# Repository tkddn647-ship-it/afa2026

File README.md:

# AFA2026 계측 시스템

학생 포뮬러 전기차(아주대학교 A-FA)의 **실차 데이터 계측 시스템**입니다.
서스펜션·가속도·인버터/BMS·조향 데이터를 STM32 한 곳에서 같은 시간축으로 모으고, Raspberry Pi를 거쳐 서버에 기록·실시간 표시·카메라 녹화까지 연결합니다.

| 항목 | 내용 |
|------|------|
| 기간 | 2025.09 ~ 2026.08 |
| 역할 | 계측 파트장 (계측 파트 2인) |
| 하드웨어 | STM32F407, Raspberry Pi 5, Cascadia 인버터 · Orion BMS 2 · Bosch LWS (CAN) |
| 소프트웨어 | C (STM32 HAL, DMA), Python (FastAPI 서버, 분석), JavaScript (대시보드) |

## 주요 결과

| 항목 | 결과 |
|------|------|
| 데이터 운용 주기 | 전송 방식을 WebSocket → UDP/TCP로 바꾸고 MCU에 링버퍼 + DMA 적용, **10 Hz → 100 Hz** |
| 신호 오류 판정 | 실주행 로그 3개(74,062행)에서 인버터 DC 전류가 팩 전류보다 약 25% 크게 기록된 것을 발견, 비율 0.80 재현으로 **CAN 스케일 계수 누락** 규명, 보정 계수 1.25 도출 |
| 계측 정확도 | 섀시 다이나모 교차 검증: 최고속도 계측 90 km/h vs 다이나모 87 km/h (**오차 약 3.4%**) |
| EMI 대응 | HV 동작 시 튀는 센서 값을 HV ON/OFF 시점 대조로 전자기 간섭으로 규명, 신호선 분리 · 차폐로 해결 |
| 분석 도구 | 주행 로그와 카메라 영상을 같은 시간축으로 맞춰 보는 도구를 만들어 섀시 · 파워트레인 파트가 주행 분석에 사용 |

## 남은 과제

- **데이터 무결성**: 로그별 샘플 누락 5~10%, 깨진 행 최대 약 0.1% → 바이너리 패킷 + CRC + 시퀀스 번호로 수신 즉시 판별
- **절대값 검증**: 두 전류의 비율은 맞췄지만 어느 쪽이 절대적으로 정확한지는 미검증 → 클램프 미터로 독립 측정
- **보안**: 팀 내부 전용이라 성능을 우선했음 → 열린 포트 최소화, SSH 키 인증, 방화벽 적용
- 펌웨어 RTOS 전환, 리니어 센서 전원 강하 원인 특정 (아래 §11, §4.2)

## 저장소 구성

| 경로 | 내용 |
|------|------|
| `device/ECU_test/` | STM32CubeIDE 프로젝트 (메인 MCU 펌웨어) |
| `device/raspberry pi 5/` | UART 수신 · 서버 전송 · 카메라 업로드 |
| `server/` | 로깅(`udp_logger`), 실시간 대시보드(`udp_realtime`), 분석 서버(`analysis_server`) |
| `hardware/26_TELEPCB/` | 텔레메트리 보드 KiCad 회로도 · PCB · 거버 |

아래부터는 다음 담당자를 위한 **설계 의도와 구현 구조** 문서입니다.

---

## 1. 한 줄 요약

> 차량의 리니어·가속도·인버터/BMS·조향 데이터를 **MCU에서 동일 타임라인으로 통합 수집(100 Hz)** 하고, UART로 Raspberry Pi에 넘겨 Hotspot Wi‑Fi로 서버에 로깅·실시간 표시·카메라 녹화까지 연결한다.  
> (현재 구현 보드는 STM32F407이며, **시간 동기화가 목적이라 Teensy 등 다른 MCU로 대체 가능** — 자세한 내용은 §5.2)

---

## 2. 전체 시스템 구조

```
[차량 센서/ECU들]                    [현장 보드]                         [네트워크]         [서버]
Linear FR/FL/RR/RL ──ADC──┐
LIS3DSH Accel ──────SPI───┤
Motor Inverter+BMS ─CAN1──┼──▶ STM32F407 MCU ──UART4 921600──▶ Raspberry Pi 5 ──Wi‑Fi──▶ Hotspot
Steering (LWS) ─────CAN2──┘         ▲                              │ Camera 15fps              │
Wheel speed (옵션) ─USART2─┘         │                              │                           ▼
                                      │                         data_send_server.py     Logger   :8000
                                      └─ 모든 텔레메트리 1차 집약                         Realtime :8011
                                                                                         Camera   :8012
```

설계의 핵심은 **“모든 차량 데이터는 먼저 MCU로 모인다”** 입니다.

| 구간 | 역할 |
|------|------|
| 센서 / CAN | 물리량·차량 버스 데이터 생성 |
| **STM32 MCU** | 샘플링·단위 환산·버퍼링·동기 타임스탬프 |
| **UART4** | MCU → Pi 단일 CSV 스트림 |
| **Raspberry Pi 5** | 파싱, 배치 HTTP 전송, 카메라 프레임 업로드 |
| **Hotspot** | 이동 환경 Wi‑Fi (아이폰 핫스팟 등으로 운용) |
| **서버** | 집 노트북에서 구동. CSV 로깅, 실시간 대시보드, 카메라 수신/녹화. 공유기 포트포워딩 + SSH로 원격 관리 |

배치도 이미지: [`afa2026_system_layout.png`](./afa2026_system_layout.png)

서버는 클라우드 전용 VM이 아니라 **집에 둔 노트북**을 서버로 쓰고, 공유기·방화벽·SSH를 열어 **밖에서도 본인 PC로 원격 접속·제어**하는 방식으로 운용했습니다. 자세한 절차는 [§8. 집 서버 원격 접속 (포트포워딩 + SSH)](#8-집-서버-원격-접속-포트포워딩--ssh) 참고.

---

## 3. 하드웨어 설계

### 3.1 MCU 보드

| 항목 | 내용 |
|------|------|
| MCU | **STM32F407** (Discovery / 커스텀 PCB 연동) |
| 클럭 | HSE 크리스털 → PLL (시스템 클럭). UART/CAN 비트 타이밍 정확도에 필요 |
| 워치독 | IWDG (~1 s) — 메인 루프 정지 시 리셋 |

### 3.2 센서·버스 핀맵 (펌웨어 기준)

#### 리니어 포텐셔미터 (서스펜션 변위)

| 채널 | MCU 핀 | ADC | 비고 |
|------|--------|-----|------|
| **FR** | PA1 | ADC1_IN1 | 3선: VCC / GND / Signal |
| **RR** | PA2 | ADC1_IN2 | |
| **RL** | PA3 | ADC1_IN3 | |
| **FL** | PA4 | ADC1_IN4 | |

- ADC 기준(VDDA)은 **3.3 V**
- 센서 공급/풀스케일 전압은 채널별로 다르며, **소프트웨어 vmax 캘리브레이션**으로 0–100 mm에 맞춤
- Discovery **PA0**은 유저 버튼용이라 리니어에 사용하지 않음

#### 가속도

| 센서 | 인터페이스 | 비고 |
|------|------------|------|
| LIS3DSH | SPI1 | ODR 상향(400 Hz급)으로 200/100 Hz 샘플에 대응 |

#### CAN

| 버스 | 속도 | 핀 (펌웨어) | 상대 |
|------|------|-------------|------|
| **CAN1** | 250 kbps | **PB8 RX / PB9 TX** | Cascadia 인버터 + Orion BMS |
| **CAN2** | 500 kbps | **PB12 / PB13** | Bosch LWS 조향 |

> 회로도/PCB와 핀이 어긋나면(예: CAN1이 PA11/PA12로만 배선) 수신이 안 됩니다. 펌웨어는 **PB8/PB9, PB12/PB13** 기준입니다.

#### UART

| 포트 | 보드레이트 | 핀 | 용도 |
|------|------------|-----|------|
| **UART4** | **921600** | PC10 TX / PC11 RX | Raspberry Pi 텔레메트리 |
| USART2 | 115200 | (휠스피드 아두이노 등) | 옵션 |

Pi 배선 (GPIO):

| STM32 | Raspberry Pi 5 |
|-------|----------------|
| PC10 (UART4 TX) | Pin 10 (GPIO15 RX) |
| PC11 (UART4 RX) | Pin 8 (GPIO14 TX) |
| GND | GND |

포트: `/dev/ttyAMA0` (`dtparam=uart0=on`)

### 3.3 전원·배치·실차 이슈 (설계 시 고려)

- MCU·Pi는 근거리(배전함 등)에 두고, 모터컨트롤러는 함 밖인 경우가 많음 → **UART 거리는 짧아 유리**, 다만 **고전류 GND/EMI**가 케이블로 타고 들어옴
- 리니어 케이블에서 **신호↔파워 교차/단락** 시 중간 위치에서도 ADC가 ~3.3 V(100 mm 고정)처럼 보임 → 하드웨어 배선 문제로 확인됨
- 플로팅 ADC 핀은 센서 미연결 시에도 중간값이 움직임 → 정상 현상
- 핫스팟 + 차량 이동 시 **Pi→서버 업로드**가 병목이 되어 로그 유효 Hz가 떨어질 수 있음 (MCU 샘플링과 별개)

---

## 4. 소프트웨어 아키텍처 (device)

### 4.1 디렉터리

```
device/
├── ECU_test/                 # STM32CubeIDE 프로젝트 (메인 MCU 펌웨어)
│   ├── Core/Inc|Src/         # 애플리케이션 코드
│   ├── Drivers/              # HAL / CMSIS
│   └── ECU_test.ioc          # CubeMX 설정
├── raspberry pi 5/           # Pi 수신·서버 전송·카메라
│   ├── Uart_stm.py           # UART CSV 파서
│   ├── data_send_server.py   # ingest / realtime 전송
│   ├── camera.py             # 카메라 프레임 업로드 (15fps 운용)
│   └── stm_ingest.env.example
├── wheel_speed/              # 휠스피드 아두이노 (옵션)
├── Fluid_Sensor/             # 유체 센서 스케치
├── esp32/ , esp32_motor_can/ # 보조/실험용
└── ...
```

### 4.2 STM32 펌웨어 — 슈퍼루프 설계

RTOS 없이 **메인 루프 + 논블로킹** 구조입니다 (`main.c`).

1. `MX_*_Init` — GPIO, CAN1/2, UART, ADC, SPI, DMA
2. `LIS3DSH` / `CAN_Vehicle` / `CAN_LWS` / `SensorUart` / `Uart4Tx` 초기화
3. 루프:
   - CAN FIFO 드레인·파싱
   - `SensorUart_Process()` — 100 Hz 샘플 적재, 20 Hz DMA flush
   - IWDG kick

#### 샘플링 / 전송

| 항목 | 값 | 파일 |
|------|-----|------|
| 샘플 주기 | **10 ms (100 Hz)** | `sensor_uart.h` / `.c` |
| UART flush | **20 Hz**, 배치 5샘플 | 동일 |
| TX | UART4 **DMA 논블로킹** | `uart4_tx.c` |
| Baud | **921600** | `usart.c` |

초기에는 200 Hz(5 ms)였으나, 실차·무선 부하를 고려해 **100 Hz**로 조정했습니다.

#### 리니어 ADC 처리 (`adc.c` / `adc.h`)

1. 채널당 **8회 평균**
2. **EMA** 필터 (노이즈 완화)
3. 전압 환산: `voltage_mv = raw × 3300 / 4095`
4. 위치 환산(채널별):

```text
position_mm = (voltage_mv / ADC_LINEAR_VMAX_xx_MV) × 100
```

풀 스트로크 실측으로 vmax를 맞춥니다. (예: 풀에서 88.6 mm가 나오면 `vmax_new = vmax_old × 0.886`)

최신 캘리 상수 예:

| 채널 | `ADC_LINEAR_VMAX_*_MV` |
|------|------------------------|
| FR | 1825 |
| RR | 1835 |
| RL | 1827 |
| FL | 1818 |

미해결 이슈 — ADC형 센서 전원 강하 원인 규명 필요: 리니어 포텐셔미터 전원부에서 3A 레귤레이터 Vout 자체는 3.3V로 정상이었으나, PCB를 지나 센서 커넥터 단에서는 2.3~2.7V까지 떨어지는 현상이 실측됐습니다. 흐르는 전류가 mA 수준(저항 분압 구조)인 점을 감안하면 컨버터 용량 부족은 아니며, Vout 이후 구간(PCB 파워 트레이스 또는 커넥터 접점)에서 비정상적으로 큰 저항이 있는 것으로 추정되는데 이게 어디가 문제인지 정확하게 확인을 못해서 소프트웨어적으로 캘리브레이션 우선 했습니다. 이 전압 강하가 vmax 캘리브레이션을 흔드는 원인이 될 수 있어, 트레이스 문제인지 커넥터 접점 문제인지 다음 담당자가 실측으로 특정해야 하는 미해결 문제입니다.

#### CAN 파싱 (`can_vehicle.c`, `can_lws.c`)

- Cascadia Motion 프로토콜(V5.9 계열): 온도·전류·전압·토크·Id/Iq·RPM 등 **int16 × 0.1** 환산 후 float 보관
- Orion BMS 커스텀 ID(0x081/0x082 등): 전압·전류·Ah·온도·CCL/DCL
- LWS: 조향각·조향 속도
- UART로 나가기 전에 **이미 공학 단위로 환산**됨 (Pi/서버에서 재스케일하지 않음)
- `can1` / `can2`: 최근 **500 ms** 내 수신 여부 (0/1)

#### UART CSV 한 줄 (순서 고정)

```text
stm_ms, FR, FL, RR, RL, x_g, y_g, z_g, ecu_temp,
steering_angle, steering_speed,
inv_temp_igt, inv_temp_motor, inv_motor_speed, inv_dc_current, inv_voltage,
motor_precharge, motor_main_contactor, motor_inverter_mode,
inv_shudder_torque, inv_id_feedback, inv_iq_feedback,
inv_torque_commanded, inv_torque_feedback, inv_id_command, inv_iq_command,
bms_charge, bms_voltage, bms_current, bms_ccl, bms_dcl, bms_temp_maxvalue, bms_capacity,
can1, can2
```

제어 라인(데이터 아님): `STM_READY`, `HB,...`, `LWS_CAL,...`

차속은 `inv_motor_speed × 0.0222328` (타이어 외경 460 mm, 감속비 3.9)로 **서버/Pi에서 계산**하는 것을 권장 (UART 필드 추가 불필요).

### 4.3 Raspberry Pi 5

| 스크립트 | 역할 |
|----------|------|
| `Uart_stm.py` | 921600 수신, CSV 파싱, 100 Hz/20 Hz 배치 개념 |
| `data_send_server.py` | 배치를 Logger `:8000/ingest` + (옵션) Realtime `:8011` 로 POST |
| `camera.py` | JPEG 프레임 업로드 (운용 **15 fps**) |
| `uart_test.py` | 보드레이트/배선 점검 |

예시:

```bash
python3 data_send_server.py \
  --port /dev/ttyAMA0 \
  --baud 921600 \
  --realtime-url http://<server>:8011/api/live/ingest
```

환경 변수 예시는 `stm_ingest.env.example` 참고.

### 4.4 서버 쪽 (연동만 요약)

| 서비스 | 포트 | 역할 |
|--------|------|------|
| `udp_logger` | 8000 | CSV 로깅 ingest |
| `udp_realtime` | 8011 | 실시간 대시보드 |
| camera | 8012 | 프레임 수신·녹화(ffmpeg) |

실차에서 로그 유효 Hz가 50대까지 떨어지는 경우, CSV의 `stm_ms`는 대부분 10 ms를 유지하는 반면 wall-clock 초당 행 수만 줄어든 패턴이 많았습니다 → **MCU 샘플링보다 Hotspot/서버 업로드·카메라 부하**가 원인인 경우가 많습니다. 센서 100 Hz를 유지하려면 카메라 fps/해상도를 먼저 낮추는 편이 유리합니다.

---

## 5. 핵심 설계 판단

### 5.1 MCU 중앙 통합 — 핵심은 “시간 동기화”

이 프로젝트에서 MCU(현재 구현은 STM32F407)를 둔 **가장 큰 이유**는 브랜드가 아니라 **시간 동기화**입니다.

- 리니어·가속도·인버터/BMS CAN·조향 CAN을 **서로 다른 장치·주기**로 받으면, 나중에 맞춰도 샘플 시각이 어긋나기 쉽습니다.
- 그래서 **한 MCU의 틱(`stm_ms` / `HAL_GetTick` 계열)으로 모든 채널을 같은 타임라인에 찍어** Pi·서버로 넘기는 구조를 택했습니다.
- Pi는 네트워크·카메라·업로드를 담당하고, **정밀 주기 샘플링·CAN 집약은 MCU**에 두는 역할 분리입니다.

| | 내용 |
|--|------|
| **선택 이유** | 서스펜션·구동·조향을 **동일 타임스탬프**로 맞춤 |
| **장점** | 단일 UART 스트림, 디버그·확장 용이, 실차 EMI 환경에서도 샘플 주기를 MCU가 책임 |
| **리스크** | MCU/UART가 단일 장애점, CSV가 길면 UART·무선 부하 증가 |

### 5.2 STM32를 꼭 고집할 필요는 없음

**“STM이어야만 한다”는 제약은 없습니다.**  
필요한 것은 대략 다음을 만족하는 **실시간 MCU**면 됩니다.

- ADC(리니어) + (가능하면) SPI/I2C 센서
- CAN 1~2채널 (인버터/BMS/조향)
- 안정적인 주기 타이머·타임스탬프
- Pi로 넘길 UART(또는 USB serial 등) 고속 스트림

그래서 예를 들면 아래도 **같은 역할의 중앙 계측 MCU**로 대체·재구현 가능합니다.

| 후보 | 메모 |
|------|------|
| **Teensy** (4.x 등) | 고속 클럭, USB/시리얼 편함, 커뮤니티 센서 예제 많음 |
| **다른 STM32** | 핀맵·Cube 설정만 맞으면 현재 구조와 가장 유사 |
| **ESP32** 계열 | Wi‑Fi 내장이라 Pi를 줄이는 실험도 가능하나, CAN·실시간·EMI는 설계 부담이 달라짐 |
| **기타 Cortex‑M / 보드** | ADC+CAN+UART만 되면 파이프라인 개념은 동일 |

지금 저장소 펌웨어는 **STM32F407 Discovery/Cube 기반**으로 작성된 **한 가지 구현**입니다.  
구조(센서·CAN → MCU 타임라인 → 시리얼 → Pi → 서버)만 유지하면 **Teensy 등 다른 MCU로 포팅해도 설계 의도는 그대로**입니다.

### 5.3 대안이었던 분산 전송

- 센서·카메라를 각자 올리거나 주기만 다르게 하는 방식
- 무선 부하는 나눌 수 있으나 **시각 동기·배선·프로토콜 복잡도**가 커짐 → 본 프로젝트 목표(동기 로깅)와는 덜 맞음

### 5.4 샘플링 100 Hz / UART 921600

- 200 Hz → 100 Hz: 루프·UART·업로드 여유
- 460800 ↔ 921600: 용량 vs EMI/배선 안정성 트레이드오프. 근거리면 921600 가능

### 5.5 리니어 캘리브레이션을 소프트웨어로

- 채널마다 풀전압이 다름 (하드웨어·케이블·장착)
- 코드에서 채널별 `vmax`로 100 mm 맞춤 — **배선 불량(신호/파워 교차)은 캘리로 고칠 수 없음**

### 5.6 텔레메트리 전송 방식의 다른 선택지

계측에서 “차 → 기록 PC/서버”로 데이터를 넘기는 방법은 팀이 제각각이라, **이 저장소 방식(MCU + Pi + Hotspot Wi‑Fi)이 유일한 정답은 아닙니다.**  
크게 보면 아래 세 갈래로 나뉩니다.

#### (A) 상용 데이터로거를 사서 쓰는 경우

- 완성품 로거에 센서/CAN을 꽂고 USB·자체 소프트웨어로 기록
- **장점:** 배선·펌웨어·동기 UI가 제품에 포함되어 있어 구현 부담이 작음
- **단점:** 가격, 커스텀 필드/서버 연동·실시간 웹 파이프라인은 제품 제약을 따름
- DIY 계측을 깊게 파고든 팀을 찾기 어려운 이유 중 하나가, **많은 팀이 이 경로로 가기 때문**입니다. 상용 로거 사용 자체는 문제 없고, 다만 **자작 MCU 파이프라인 노하우를 물어볼 상대는 상대적으로 적습니다.**

#### (B) 본 프로젝트 — MCU 집약 + Pi + Hotspot(Wi‑Fi/인터넷)

- MCU가 동기 샘플 → UART → Pi → Hotspot → 집 서버
- **장점:** 필드·서버·카메라를 자유롭게 확장, 비용 대비 커스터마이즈
- **단점:** 무선은 Hotspot/공유기 품질에 민감, 직접 디버깅·보안·전원 설계가 필요

#### (C) UART형 장거리 무선 모듈 — 예: **EBYTE E220-900T22S**

일부 팀은 Wi‑Fi/휴대폰 핫스팟 대신, MCU(또는 중간 보드)의 **UART에 LoRa 계열 무선 시리얼 모듈**을 달아 송수신합니다.

| 항목 | E220-900T22S 요약 ([Ebyte 제품 페이지](https://www.cdebyte.com/products/E220-900T22S)) |
|------|------|
| 종류 | LoRa 기반 **무선 시리얼(UART) 모듈** (LLCC68) |
| 주파수 | 약 **850.125 ~ 930.125 MHz** (기본 예: 873.125 MHz, 868/915 MHz 대역 운용) |
| 출력 | 최대 **22 dBm** |
| 공칭 거리 | 개활지 기준 **수 km**급 (안테나·속도·환경에 크게 좌우) |
| 공중 전송률 | 대략 **2.4 kbps ~ 62.5 kbps** (설정에 따라) — **Wi‑Fi보다 훨씬 느림** |
| 인터페이스 | TTL UART (3.3 V 로직), MCU 시리얼에 붙이는 형태 |

**어떻게 쓰이나 (개념):**

```text
[차량 MCU] --UART--> [E220 송신]  ~~~900MHz LoRa~~~  [E220 수신] --UART--> [기록 PC / 다른 MCU]
```

- Hotspot·공유기·인터넷 없이도 **차 ↔ 피트/노트북** 직통에 가깝게 쓸 수 있는 선택지
- 다만 공중 속도가 낮아 **본 프로젝트처럼 긴 CSV를 100 Hz로 풀 스트리밍**하기엔 대역이 부족할 수 있음  
  → 보통은 **샘플 주기·필드 축소, 배치/압축, 또는 로컬 SD에 풀레이트 저장 + 무선은 요약/저속** 같은 설계가 필요
- 주파수·출력은 **해당 국가 전파 규정**을 반드시 확인할 것 (무단 고출력·비허가 대역 사용 금지)

본 저장소는 **(B) Wi‑Fi/Hotspot 경로를 구현·문서화**한 것이며, **(C) E220-900T22S 같은 UART LoRa 모듈 통신도 업계·동계에서 쓰이는 다른 갈래**라는 점만 참고용으로 남깁니다.  
이 레포에 E220 드라이버/설정 코드는 포함되어 있지 않습니다.

---

## 6. 디버그 체크리스트

### STM Live Expressions 예

```text
adc_linear_readings[0..3]   // FR,RR,RL,FL
adc_debug_raw[i]
g_can_vehicle_state.rx_total
g_lws_state.rx_count
uart4_tx_overflow
sensor_uart_overflow
main_loop_count
```

### 증상별

| 증상 | 우선 의심 |
|------|-----------|
| ADC만 나오고 CAN 0 | CAN 배선/트랜시버/핀맵, `can1`/`can2` |
| 중간인데 리니어 100 고정, raw≈4095 | 신호선–VCC 단락/교차 |
| 미연결 채널 값이 튐 | 플로팅 핀 (정상) |
| 로그 Hz만 떨어짐, `stm_ms`는 ~10 ms | Pi→서버 Wi‑Fi / 카메라 부하 |
| -553 mm 등 이상값 다수 | UART 줄 깨짐·컬럼 밀림 |

---

## 7. 빌드·플래시·실행

### STM32

1. STM32CubeIDE에서 `device/ECU_test` 오픈
2. Build → Debug/Run으로 보드에 플래시
3. UART4 921600, CAN 핀맵이 배선과 일치하는지 확인

### Raspberry Pi

```bash
cd "device/raspberry pi 5"
pip install pyserial requests
python3 data_send_server.py --port /dev/ttyAMA0 --baud 921600
```

카메라:

```bash
python3 camera.py --fps 15
```

---

## 8. 집 서버 원격 접속 (포트포워딩 + SSH)

계측 서버(`udp_logger` / `udp_realtime` / camera 등)는 **집 PC(노트북)** 에서 돌리고, 현장(차·Pi)은 Hotspot Wi‑Fi로 그 서버에 데이터를 올립니다.  
서버 노트북은 항상 옆에 둘 수 없으므로, **집 공유기 포트포워딩 + OS 방화벽에서 SSH(22) 허용**해 두고, 밖에서는 **공인 IP 또는 DDNS 도메인**으로 SSH 접속해 노트북을 원격 제어했습니다.

### 8.1 전체 흐름

```text
[밖: 본인 노트북 / 폰]
        │  ssh user@<공인IP또는도메인> -p 22
        ▼
[인터넷]
        ▼
[집 공유기]  ── 포트포워딩: 외부 22 → 서버노트북 사설IP:22
        │         (필요 시 8000/8011/8012 등 HTTP도 포워딩)
        ▼
[서버 노트북]  OpenSSH 서버 수신
        │
        ├─ 터미널로 서비스 재시작, 로그 확인, 코드 pull …
        └─ (터널/브라우저) 로거·실시간 페이지 점검
```

즉 **“서버 = 집 노트북”** 이고, **“원격 = SSH로 그 노트북에 들어가 조작”** 입니다.

### 8.2 서버 노트북 준비 (SSH 서버)

1. OS에 **OpenSSH Server** 설치·활성화  
   - Linux: `openssh-server` 설치 후 `sshd` 기동  
   - Windows: 선택적 기능에서 OpenSSH 서버 사용 가능
2. 로그인할 **계정/비밀번호 또는 SSH 키** 준비 (키 인증 권장)
3. 노트북이 절전으로 네트워크가 끊기지 않게 **절전/디스플레이 끄기 설정** 조정
4. 가능하면 공유기 DHCP에서 서버 PC에 **고정 사설 IP** (예: `192.168.0.50`) 예약

접속 예:

```bash
ssh <username>@<공인IP또는도메인>
# 포트가 22가 아니면
ssh -p <포트> <username>@<공인IP또는도메인>
```

접속되면 집 노트북 셸이 열리고, 여기서 `server/` 서비스 기동·재시작·로그 확인 등 **원격으로 서버를 조종**할 수 있습니다.

### 8.3 OS 방화벽 — 22번(SSH) 허용

노트북 방화벽에서 **인바운드 TCP 22** 를 허용해야 공유기까지 들어온 SSH가 PC에 도달합니다.

- Linux (`ufw` 예): `sudo ufw allow 22/tcp` 후 `sudo ufw enable`
- Windows: Windows Defender 방화벽 → 인바운드 규칙에서 OpenSSH(또는 TCP 22) 허용

계측 HTTP도 밖에서도 열려야 하면 동일하게 **8000 / 8011 / 8012** 등을 허용합니다.  
(현장 Pi → 서버만 쓰고, 본인은 SSH만 쓸 계획이면 HTTP는 LAN 전용으로 두고 SSH 터널로만 볼 수도 있습니다.)

### 8.4 집 공유기 포트포워딩

공유기 관리 페이지(보통 `192.168.0.1` / `192.168.1.1`)에서:

| 항목 | 설정 예 |
|------|---------|
| 서비스 이름 | SSH |
| 외부(WAN) 포트 | **22** (또는 보안상 다른 포트로 바꿔 내부 22로 변환) |
| 내부 IP | 서버 노트북 사설 IP |
| 내부 포트 | **22** |
| 프로토콜 | TCP |

추가로 로거/실시간/카메라를 외부에서 직접 열려면:

| 외부 포트 | 내부 | 용도 |
|-----------|------|------|
| 8000 | 노트북:8000 | Logger ingest / CSV |
| 8011 | 노트북:8011 | Realtime |
| 8012 | 노트북:8012 | Camera |

Pi의 `--url` / `--realtime-url` 에는 **공유기 공인 IP 또는 DDNS 도메인**을 넣습니다.  
예: `http://<your-domain>.ddns.net:8000/ingest`

### 8.5 공인 IP vs 도메인 (DDNS)

- **고정 공인 IP**면 IP로 바로 `ssh user@x.x.x.x`
- 가정용 회선은 IP가 자주 바뀌므로 **DDNS 도메인**(공유기 내장 DDNS 또는 외부 DDNS)을 묶어 두는 편이 편함  
  → 현장·원격 모두 `도메인:포트`로 접속·ingest

Pi/노트북이 Hotspot에 있어도, **목적지가 집 공인 IP/도메인**이면 인터넷 경유로 집 서버에 도달합니다.

### 8.6 실제로 한 일 (운용)

1. 집 노트북에 서버 스택 실행 (`start_servers.sh` 등)
2. 공유기에서 **22 → 노트북**, 필요 시 **8000/8011/8012** 포워딩
3. 노트북 방화벽에서 해당 포트 허용
4. 밖(또는 차 근처)에서 **SSH로 집 노트북 접속** → 서비스 상태 확인, 재시작, 설정 수정
5. 현장 Pi는 Hotspot으로 인터넷 올린 뒤, **도메인/공인 IP의 ingest URL**로 데이터·카메라 전송

이 구성으로 **서버 노트북을 집에 둔 채 원격으로 제어**하며 계측 파이프라인을 유지했습니다.

### 8.7 보안 주의 (필수)

- SSH를 인터넷에 열면 **무차별 대입 공격** 대상이 됩니다.
  - 가능하면 **키 인증만** 허용, 비밀번호 로그인 비활성
  - 외부 SSH 포트를 22 대신 **임의 포트**로 포워딩
  - `fail2ban` 등 차단, 강한 비밀번호/키 사용
- 공유기·PC 관리자 비밀번호를 기본값으로 두지 말 것
- README/깃에 **실제 공인 IP·계정·비밀번호·개인 도메인 크리덴셜을 올리지 말 것**
- 장기간 안 쓰면 포워딩·방화벽 규칙을 끄는 것을 권장

---

## 9. 라이선스 / 주의

- STM HAL/CMSIS는 ST 라이선스 조건을 따릅니다.
- `.env` / 실제 ingest URL·자격 증명은 커밋하지 마세요. `*.env.example`만 사용하세요.
- `Debug/` 빌드 산출물, `__pycache__`, 셸 히스토리는 저장소에서 제외하는 것을 권장합니다.
- 집 서버 SSH/포트포워딩은 편리하지만 노출면이 생기므로 [§8.7](#87-보안-주의-필수)을 지키세요.

---

## 10. 변경 이력 (device 관점 요약)

- STM32 슈퍼루프 + CAN1/2 파싱 + UART CSV 파이프라인
- 리니어 ADC  Averaging/EMA + 채널별 vmax 캘리
- UART DMA TX, baud 921600, 샘플 100 Hz / flush 20 Hz
- Pi `Uart_stm` / `data_send_server` / 카메라 연동
- `can1`/`can2` 링크 플래그, 인버터 토크·Id/Iq 필드 확장
- 실차 EMI·케이블·핫스팟 병목 경험을 반영한 운용 가이드
- 집 노트북 서버 + 공유기 포트포워딩 + SSH(22) 원격 제어 운용 문서화
- MCU 채택 이유(시간 동기화) 명시, STM 외 Teensy 등 대체 가능 안내
- 텔레메트리 대안: 상용 로거 / Wi‑Fi·Hotspot / EBYTE E220-900T22S(UART LoRa) 비교 정리

## 11. 아쉬운점
RTOS 미적용 — 시간 부족으로 남은 아쉬운 점
현재 펌웨어는 RTOS 없이 메인 루프 + DMA/인터럽트 구조입니다. CAN 수신, UART 송신 등 타이밍이 중요한 부분은 이미 DMA·인터럽트로 처리되고 있어서, RTOS가 없다고 해서 당장 샘플링 타이밍이 깨지는 구조는 아닙니다.
다만 기능이 하나씩 늘어나면서 메인 루프 안에 로직이 계속 쌓이는 구조가 됐고, 시간이 있었다면 FreeRTOS 등으로 태스크를 나눠서(센서 샘플링 태스크, CAN 파싱 태스크, UART 송신 태스크 등) 더 깔끔하게 모듈화하고 싶었던 부분입니다. 단순히 시간이 부족해서 모듈화 리팩터링까지 못 간 것이 아쉽습니다.

하드웨어 모듈화 - 시간 부족
실제 계측 장비(데이터로거)처럼 만들고싶었지만, 시간문제와 당시 지식이 조금 모자랐기에 장비화(?)는 못했습니다... 실제로 시중에 파는 계측장비처럼 제작이 가능하다면 진짜 가능할 것 같긴한데 아무튼 가능하다면 매번 안바꿔도 되는 부분이라 이거 성공하면 진짜 히트입니다.

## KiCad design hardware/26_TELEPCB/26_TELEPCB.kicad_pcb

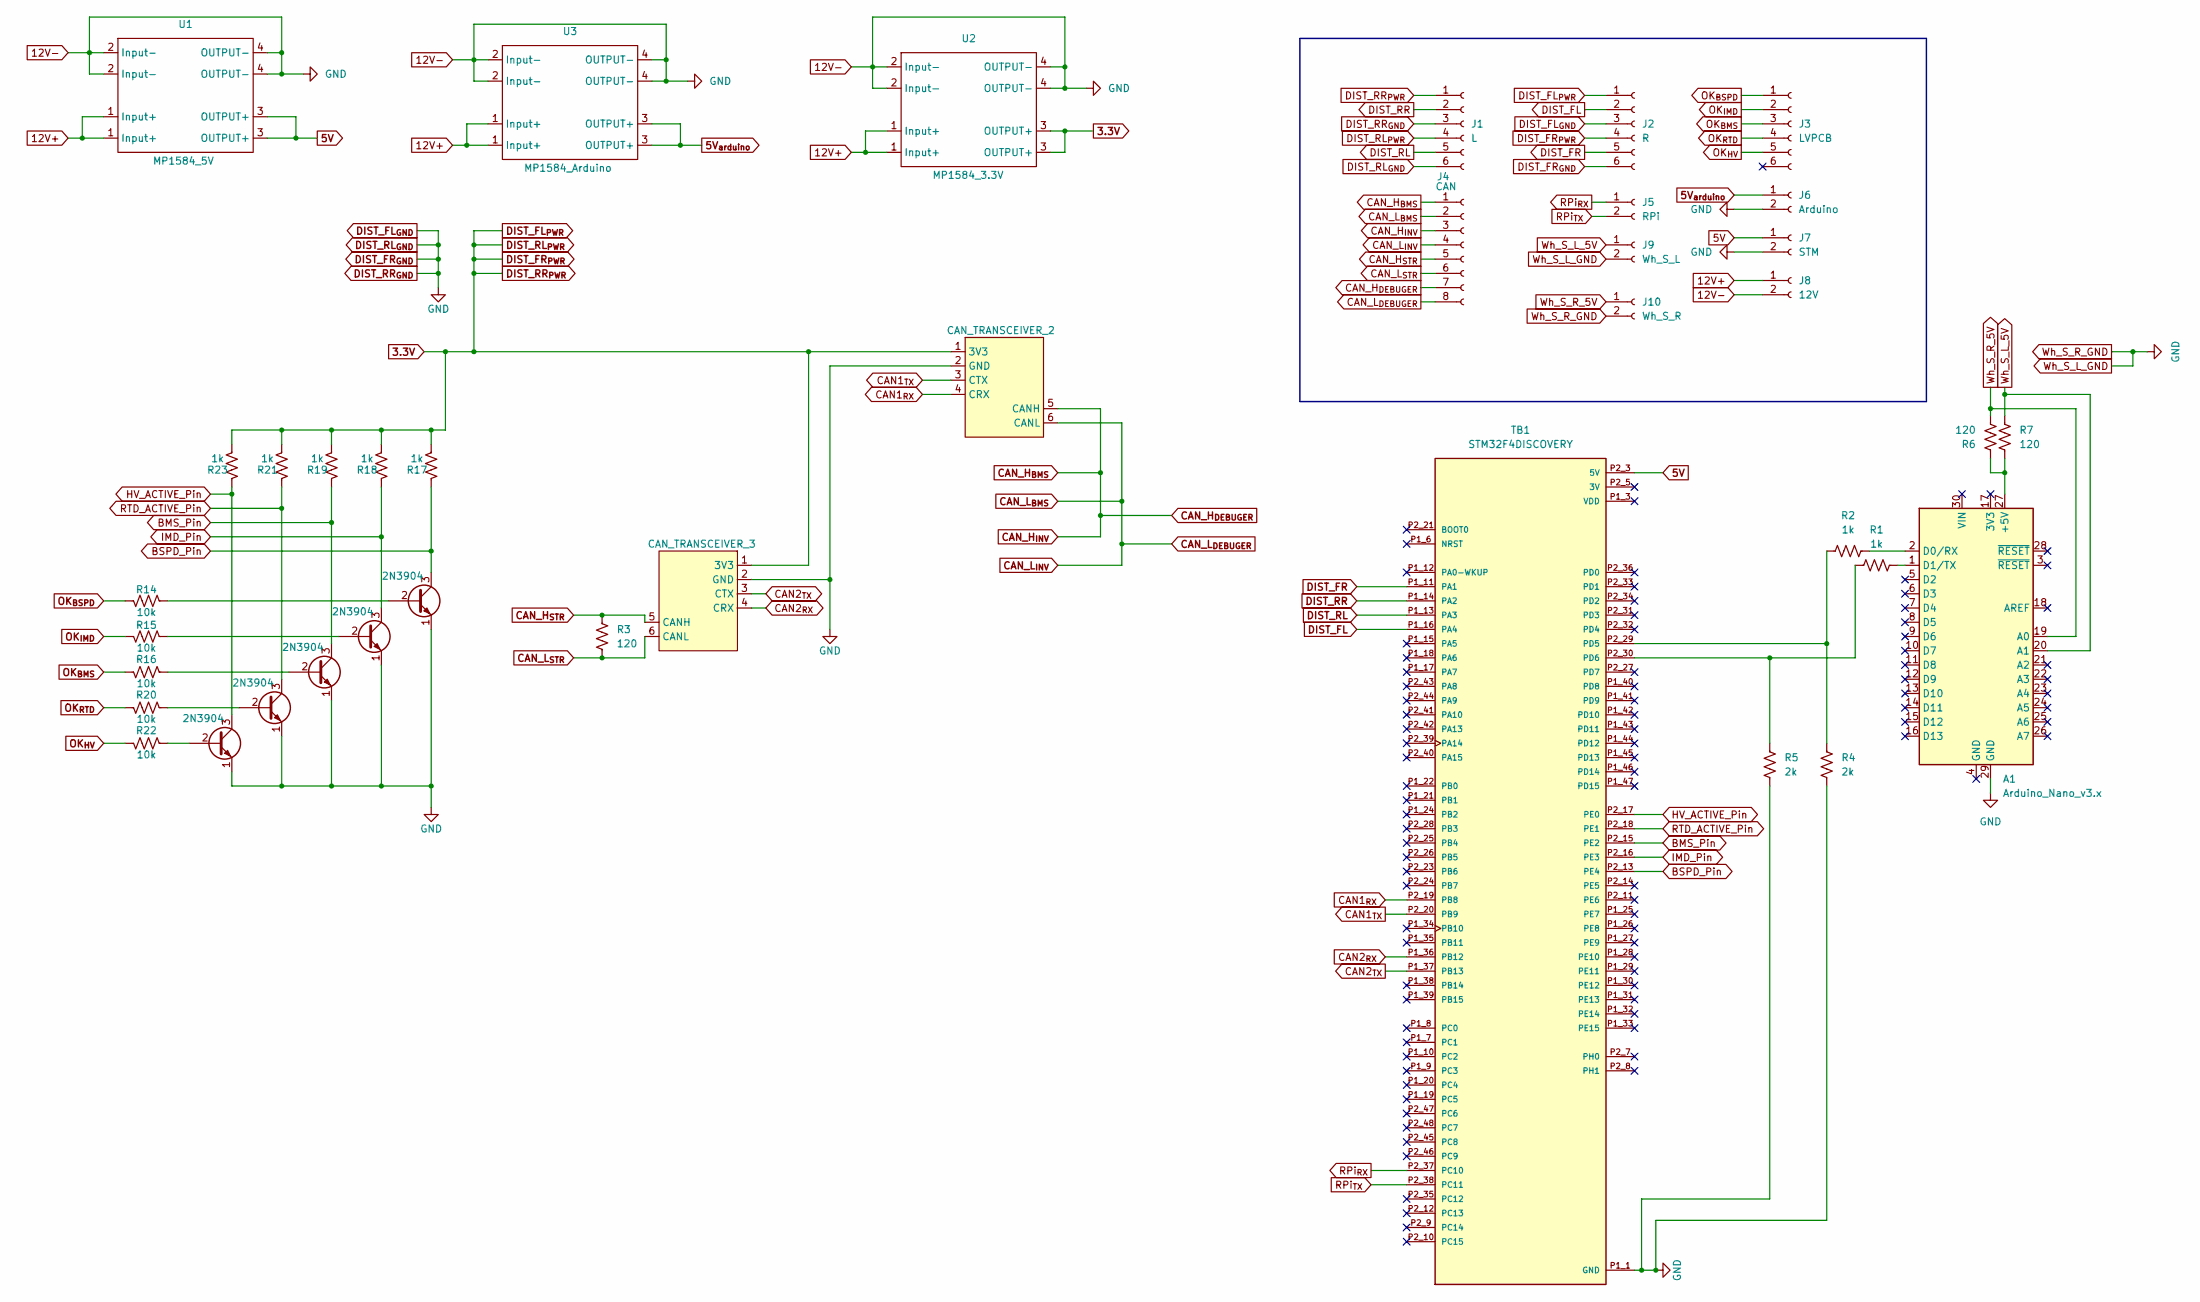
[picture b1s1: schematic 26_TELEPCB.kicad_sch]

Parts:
A1: Arduino_Nano_v3.x; Arduino_Nano
J1: L; Molex_SPOX_5267-06A_1x06_P2.50mm_Vertical
J2: R; Molex_SPOX_5267-06A_1x06_P2.50mm_Vertical
J3: LVPCB; Molex_SPOX_5267-06A_1x06_P2.50mm_Vertical
J4: CAN; Molex_SPOX_5267-08A_1x08_P2.50mm_Vertical
J5: RPi; Molex_Mini-Fit_Jr_5566-02A_2x01_P4.20mm_Vertical
J6: Arduino; Molex_Mini-Fit_Jr_5566-02A_2x01_P4.20mm_Vertical
J7: STM; Molex_Mini-Fit_Jr_5566-02A_2x01_P4.20mm_Vertical
J8: 12V; Molex_Mini-Fit_Jr_5566-02A_2x01_P4.20mm_Vertical
J9: Wh_S_L; Molex_Mini-Fit_Jr_5566-02A_2x01_P4.20mm_Vertical
J10: Wh_S_R; Molex_Mini-Fit_Jr_5566-02A_2x01_P4.20mm_Vertical
Q6, Q7, Q8, Q9, Q10: 2N3904; TO-92_Inline_Wide
R1, R2: 1k; R_Axial_DIN0207_L6.3mm_D2.5mm_P7.62mm_Horizontal
R3, R6, R7: 120; R_Axial_DIN0207_L6.3mm_D2.5mm_P7.62mm_Horizontal
R4, R5: 2k; R_Axial_DIN0207_L6.3mm_D2.5mm_P7.62mm_Horizontal
R14, R15, R16, R20, R22: 10k; R_1206_3216Metric_Pad1.30x1.75mm_HandSolder
R17, R18, R19, R21, R23: 1k; R_1206_3216Metric_Pad1.30x1.75mm_HandSolder
TB1: STM32F4DISCOVERY; MODULE_STM32F4DISCOVERY; PARTREV 6
U1: MP1584_5V; SRT_MPT1584EN_Module
U2: MP1584_3.3V; SRT_MPT1584EN_Module
U3: MP1584_Arduino; SRT_MPT1584EN_Module
U9: CAN_TRANSCEIVER_3; CAN_TRANSIVER
U11: CAN_TRANSCEIVER_2; CAN_TRANSIVER

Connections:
3.3V: J1.1, J1.4, J2.1, J2.4, R17.1, R18.1, R19.1, R21.1, R23.1, U2.3 (OUTPUT+), U9.1 (3V3), U11.1 (3V3)
5V: J7.1, TB1.P2_3 (5V), TB1.P2_4 (5V), U1.3 (OUTPUT+)
5V_{arduino}: J6.1, U3.3 (OUTPUT+)
12V+: J8.1, U1.1 (Input+), U2.1 (Input+), U3.1 (Input+)
12V-: A1.29 (GND), J1.3, J1.6, J2.3, J2.6, J6.2, J7.2, J8.2, J9.2, J10.2, Q6.1 (E), Q7.1 (E), Q8.1 (E), Q9.1 (E), Q10.1 (E), R4.2, R5.2, TB1.P1_1 (GND), TB1.P1_2 (GND), TB1.P1_5 (GND), TB1.P1_23 (GND), TB1.P1_49 (GND), TB1.P1_50 (GND), TB1.P2_1 (GND), TB1.P2_2 (GND), TB1.P2_49 (GND), TB1.P2_50 (GND), U1.2 (Input-), U1.4 (OUTPUT-), U2.2 (Input-), U2.4 (OUTPUT-), U3.2 (Input-), U3.4 (OUTPUT-), U9.2 (GND), U11.2 (GND)
BMS_Pin: Q6.3 (C), R19.2, TB1.P2_15 (PE2)
BSPD_Pin: Q8.3 (C), R17.2, TB1.P2_13 (PE4)
CAN1_{RX}: TB1.P2_19 (PB8), U11.4 (CRX)
CAN1_{TX}: TB1.P2_20 (PB9), U11.3 (CTX)
CAN2_{RX}: TB1.P1_36 (PB12), U9.4 (CRX)
CAN2_{TX}: TB1.P1_37 (PB13), U9.3 (CTX)
CAN_H_{BMS}: J4.1, J4.3, J4.7, U11.5 (CANH)
CAN_H_{STR}: J4.5, R3.1, U9.5 (CANH)
CAN_L_{BMS}: J4.2, J4.4, J4.8, U11.6 (CANL)
CAN_L_{STR}: J4.6, R3.2, U9.6 (CANL)
DIST_FL: J2.2, TB1.P1_16 (PA4)
DIST_FR: J2.5, TB1.P1_11 (PA1)
DIST_RL: J1.5, TB1.P1_13 (PA3)
DIST_RR: J1.2, TB1.P1_14 (PA2)
HV_ACTIVE_Pin: Q10.3 (C), R23.2, TB1.P2_17 (PE0)
IMD_Pin: Q7.3 (C), R18.2, TB1.P2_16 (PE3)
unnamed: A1.27 (+5V), R6.1, R7.2
unnamed: A1.2 (D0/RX), R2.2
unnamed: A1.1 (D1/TX), R1.2
unnamed: Q6.2 (B), R16.2
unnamed: Q7.2 (B), R15.2
unnamed: Q8.2 (B), R14.2
unnamed: Q9.2 (B), R20.2
unnamed: Q10.2 (B), R22.2
unnamed: R2.1, R4.1, TB1.P2_29 (PD5)
unnamed: R1.1, R5.1, TB1.P2_30 (PD6)
OK_{BMS}: J3.3, R16.1
OK_{BSPD}: J3.1, R14.1
OK_{HV}: J3.5, R22.1
OK_{IMD}: J3.2, R15.1
OK_{RTD}: J3.4, R20.1
RPi_{RX}: J5.1, TB1.P2_37 (PC10)
RPi_{TX}: J5.2, TB1.P2_38 (PC11)
RTD_ACTIVE_Pin: Q9.3 (C), R21.2, TB1.P2_18 (PE1)
Wh_S_L_5V: A1.20 (A1), J9.1, R7.1
Wh_S_R_5V: A1.19 (A0), J10.1, R6.2

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
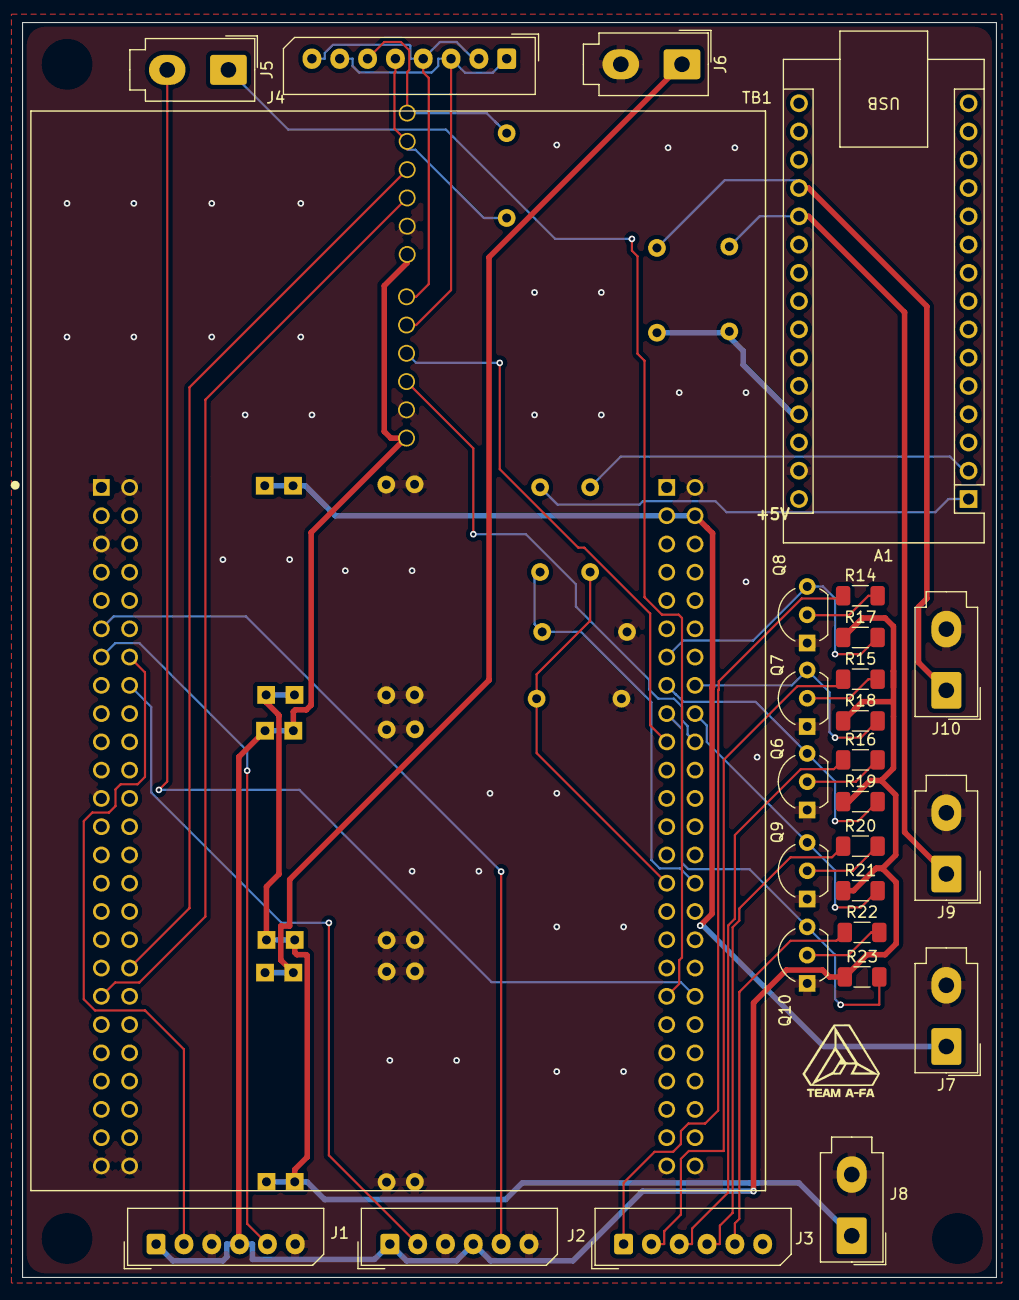
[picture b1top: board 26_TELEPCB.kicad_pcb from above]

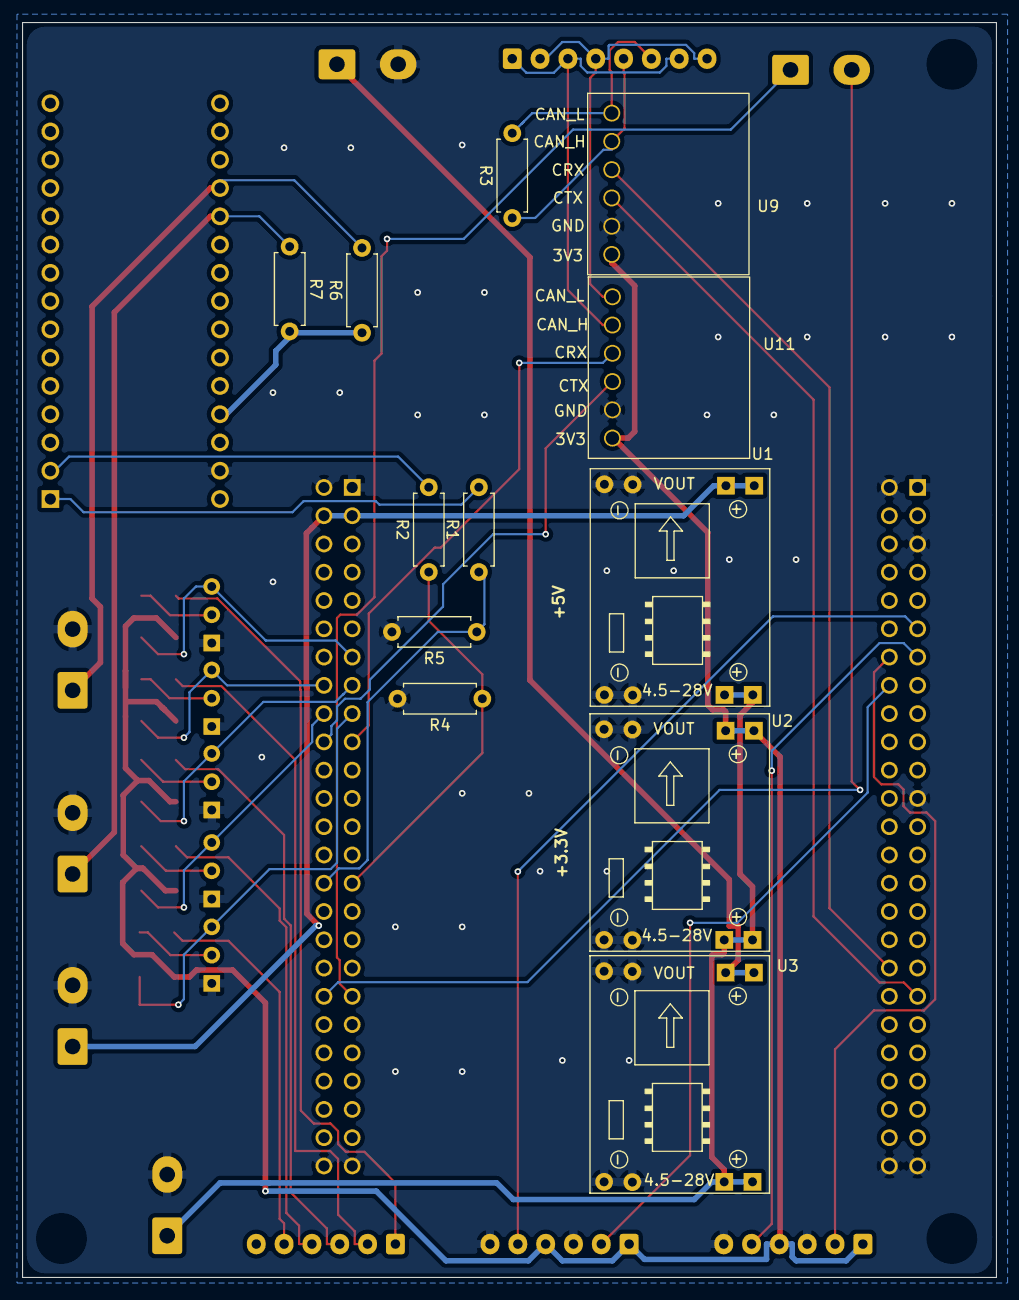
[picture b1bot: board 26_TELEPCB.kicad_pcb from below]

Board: 2 copper layers, 87.5 x 112.8 mm, 39 parts (12 on the bottom side), 41 nets.

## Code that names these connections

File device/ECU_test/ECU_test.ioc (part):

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Mcu.Name=STM32F407V(E-G)Tx
Mcu.Package=LQFP100
Mcu.UserName=STM32F407VGTx
PA0-WKUP.Signal=GPIO_Input
PA1.Signal=ADCx_IN1
PA2.Signal=ADCx_IN2
PA3.Signal=ADCx_IN3
PA4.Signal=ADCx_IN4
PA5.Mode=Full_Duplex_Master
PA5.Signal=SPI1_SCK
PA6.Mode=Full_Duplex_Master
PA6.Signal=SPI1_MISO
PA7.Mode=Full_Duplex_Master
PA7.Signal=SPI1_MOSI
PB12.Mode=CAN_Activate
PB12.Signal=CAN2_RX
PB13.Mode=CAN_Activate
PB13.Signal=CAN2_TX
PB8.Mode=CAN_Activate
PB8.Signal=CAN1_RX
PB9.Mode=CAN_Activate
PB9.Signal=CAN1_TX
PC10.GPIOParameters=GPIO_Label
PC10.GPIO_Label=Raspberry pi 5 to RX
PC10.Mode=Asynchronous
PC10.Signal=UART4_TX
PC11.GPIOParameters=GPIO_Label
PC11.GPIO_Label=Raspberry pi 5 to TX
PC11.Mode=Asynchronous
PC11.Signal=UART4_RX
PC14-OSC32_IN.Mode=LSE-External-Oscillator
PC14-OSC32_IN.Signal=RCC_OSC32_IN
PC15-OSC32_OUT.Mode=LSE-External-Oscillator
PC15-OSC32_OUT.Signal=RCC_OSC32_OUT
PD5.GPIOParameters=GPIO_Label
PD5.GPIO_Label=Uno to RX
PD5.Mode=Asynchronous
PD5.Signal=USART2_TX
PD6.GPIOParameters=GPIO_Label
PD6.GPIO_Label=Uno to TX
PD6.Mode=Asynchronous
PD6.Signal=USART2_RX
PE0.GPIOParameters=GPIO_Label
PE0.GPIO_Label=HV_ACTIVE
PE0.Signal=GPIO_Input
PE1.GPIOParameters=GPIO_Label
PE1.GPIO_Label=RTD_ACTIVE
PE1.Signal=GPIO_Input
PE2.GPIOParameters=GPIO_Label
PE2.GPIO_Label=BMS_FAULT
PE2.Signal=GPIO_Input
PE3.GPIOParameters=GPIO_Label
PE3.GPIO_Label=IMD_FALUT
PE3.Signal=GPIO_Input
PE4.GPIOParameters=GPIO_Label
PE4.GPIO_Label=BSPD_FALUT
PE4.Signal=GPIO_Input
PH0-OSC_IN.Mode=HSE-External-Oscillator
PH0-OSC_IN.Signal=RCC_OSC_IN
PH1-OSC_OUT.Mode=HSE-External-Oscillator
PH1-OSC_OUT.Signal=RCC_OSC_OUT
RCC.HSE_VALUE=8000000
RCC.SYSCLKFreq_VALUE=168000000
RCC.SYSCLKSource=RCC_SYSCLKSOURCE_PLLCLK
board=custom

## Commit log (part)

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2026-03-07 Add server and web
